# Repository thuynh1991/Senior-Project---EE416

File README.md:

# Senior-Project---EE416: Leak Detection System for the Robosub Autonomous Submarine
Ensuring the protection of electronics is an integral portion of any electromechanical system. Our project goal is to protect electronics within the hull of the WSU Robosub Club’s autonomous submarine, by implementing methods of leak detection. Providing information of an onboard leak allows for preventative action, and could potentiallysave thousands of dollars worth of material onboard. We have developed a two-part procedure to check, and monitor for potential leaks. This procedure consists of testing for leaks before the submarine is submerged, and is followed by an internal system that monitors water infiltration while underway. This project has met the needs and requirements set by our clients and stakeholders, while maintaining freedom of engineering design interpretation.<br /><br />
The DS_LC234X is FTDI - USB connector and we will use atmega1284P-AU chip for the project. <br />
EE415 code: Code to test the leak before submarine is submerged. <br />
EE416 code: Code for the internal(onboard) system. <br />  
Aruino Nano Shield: is our back up plan in case the internal system is fail.

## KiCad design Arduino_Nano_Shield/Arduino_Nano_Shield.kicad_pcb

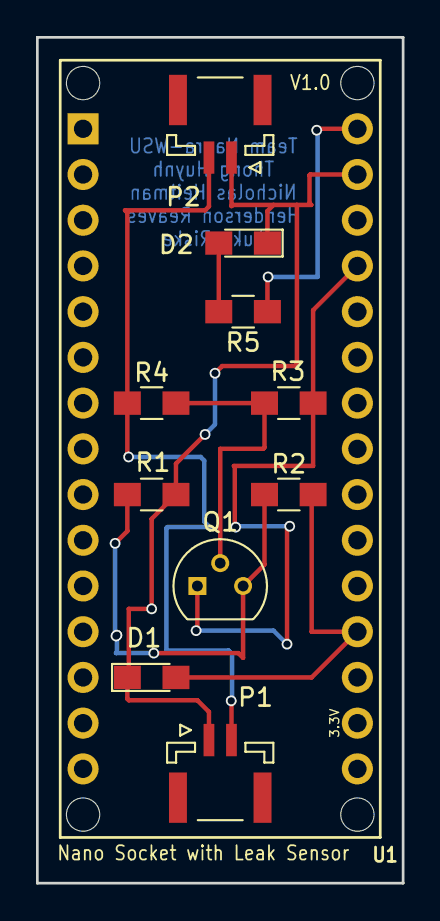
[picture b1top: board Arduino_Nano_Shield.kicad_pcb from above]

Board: 2 copper layers, 20.3 x 47.0 mm, 11 parts (0 on the bottom side), 8 nets.

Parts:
D1, D2: LED; LED_0805_HandSoldering
P1, P2: Probe_Port; JST_GH_SM02B-GHS-TB_02x1.25mm_Angled
Q1: 2N3906; TO-92_Molded_Narrow
R1, R4: 1K; R_0805_HandSoldering
R2, R5: 220; R_0805_HandSoldering
R3: 27K; R_0805_HandSoldering
U1: Arduino_Nano_Socket

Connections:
+5V: Q1.1, R3.1, U1.5V
/SIGNAL: D1.2, R2.2, U1.A0
GND: D1.1, D2.1, P1.1, P2.1, R1.2, U1.GND2
unnamed: D2.2, R5.2
unnamed: Q1.2, R3.2, R4.2
unnamed: Q1.3, R1.1, R2.1
PROBE: P1.2, P2.2, R4.1
VCC: R5.1, U1.VIN

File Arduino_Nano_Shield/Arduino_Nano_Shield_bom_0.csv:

Component,Description,Part,References,Value,Footprint,Quantity Per PCB,Datasheet,Digikey
1,LED generic,LED,D1 D2,LED,LED_0805_HandSoldering,4,,L62501CT-ND; 1516-1085-1-ND
2,,Probe_Port,P1 P2,Probe_Port,JST_GH_SM02B-GHS-TB_02x1.25mm_Angled,6,,455-1564-1-ND
3,"-40V Vce, -0.2A Ic, PNP, Small Signal Transistor, TO-92",2N3906,Q1,2N3906,TO-92_Molded_Narrow,2,https://www.fairchildsemi.com/datasheets/2N/2N3906.pdf,2N3906CS-ND
4,Resistor,R,R1 R4,1K,R_0805_HandSoldering,10,,P1.0KDACT-ND
5,Resistor,R,R2 R5,220,R_0805_HandSoldering,10,,408-1779-1-ND
6,Resistor,R,R3,27K,R_0805_HandSoldering,10,,P27KDACT-ND
7,,Arduino_Nano_Socket,U1,Arduino_Nano_Socket,Arduino_Nano_Socket,2,,S7013-ND 
,,,,,,,,
,,,,,,,,
,,,,,,,,
,,,,,,,,
,,,,,,,,
Component Groups:,7,,,,,,,
Component Count:,11,,,,,,,
Fitted Components:,11,,,,,,,
Number of PCBs:,1,,,,,,,
Total components:,11,,,,,,,
Schematic Version:,0,,,,,,,
Schematic Date:,3/25/2018,,,,,,,
BoM Date:,4/4/2018 23:13,,,,,,,
Schematic Source:,C:\Users\Thong_Huynh\Desktop\EE 416_new\Arduino_Nano_Shield\Arduino_Nano_Shield.sch,,,,,,,
KiCad Version:,Eeschema 4.0.7,,,,,,,

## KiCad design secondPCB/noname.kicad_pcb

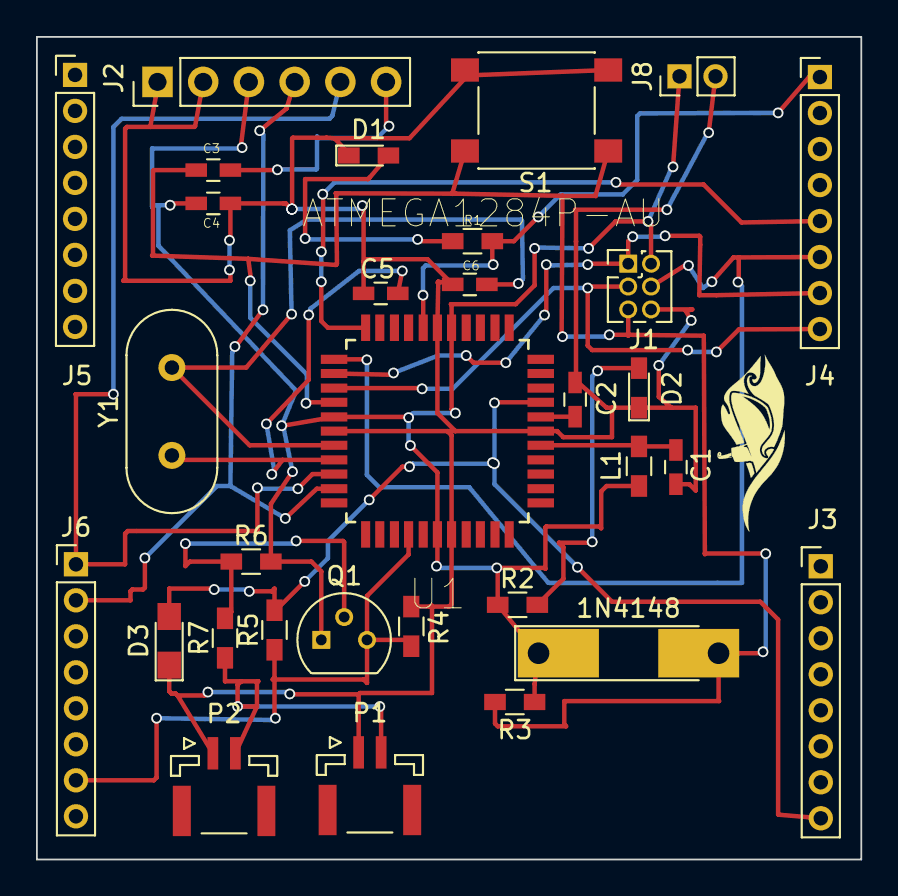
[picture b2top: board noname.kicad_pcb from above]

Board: 2 copper layers, 45.8 x 45.7 mm, 31 parts (0 on the bottom side), 21 nets.

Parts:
1N4148: D1; D_MELF-RM10_Universal_Handsoldering
C1: 100nF; C_0603_HandSoldering
C2, C4: 0.1uF; C_0603_HandSoldering
C3: 10uF; C_0603_HandSoldering
C5, C6: 22pF; C_0603_HandSoldering
D1, D2: LED_Small; LED_0603_HandSoldering
D3: LED; LED_0805_HandSoldering
J1: AVR_ISP; Pin_Header_Straight_2x03_Pitch1.27mm
J2: FTDI; Socket_Strip_Straight_1x06_Pitch2.54mm
J3: PortA; Pin_Header_Straight_1x08_Pitch2.00mm
J4: PortB; Pin_Header_Straight_1x08_Pitch2.00mm
J5: PortC; Pin_Header_Straight_1x08_Pitch2.00mm
J6: PortD; Pin_Header_Straight_1x08_Pitch2.00mm
J8: Power; Pin_Header_Straight_1x02_Pitch2.00mm
L1: 10uH; L_0603_HandSoldering
P1, P2: Probe_Port; JST_GH_SM02B-GHS-TB_02x1.25mm_Angled
Q1: 2N3906; TO-92_Molded_Narrow
R1: 330R; R_0603_HandSoldering
R2, R5: 220; R_0603_HandSoldering
R3: 10K; R_0603_HandSoldering
R4, R7: 1k; R_0603_HandSoldering
R6: 27k; R_0603_HandSoldering
S1: SW_Push; SW_SPST_PTS645
U1: ATMEGA1284P-AU; QFP80P1200X1200X120-44N
Y1: 16MHz; Crystal_HC49-U_Vertical

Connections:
/ANALOG_SIGNAL: D3.2, J3.8, R5.2, U1.30
/SIGNAL: J6.7, Q1.3, R4.1, R5.1, U1.15
AVCC: C1.1, L1.1, U1.27
GND: C1.2, C2.2, C3.2, C5.1, C6.1, D1.1, D2.1, D3.1, J1.6, J2.1, J2.2, J8.2, P1.1, P2.1, R4.2, S1.1, U1.6, U1.18, U1.28, U1.39
unnamed: C2.1, U1.29
unnamed: C4.1, J2.6
unnamed: D1.2, R1.1
unnamed: D2.2, R2.2
unnamed: Q1.2, R6.1, R7.2
PB0: J4.1, R1.2, U1.40
PB4: J4.5, U1.44
PB5: J1.4, J4.6, U1.1
PB6: J1.1, J4.7, U1.2
PB7: J1.3, J4.8, U1.3
PD0: J2.5, J6.1, U1.9
PD1: J2.4, J6.2, U1.10
PROBE: P1.2, P2.2, R7.1
RST: 1N4148.2, C4.2, J1.5, R3.1, S1.2, U1.4
VCC: 1N4148.1, C3.1, J1.2, J2.3, J8.1, L1.2, Q1.1, R2.1, R3.2, R6.2, U1.5, U1.17, U1.38
XTAL1: C5.2, U1.8, Y1.1
XTAL2: C6.2, U1.7, Y1.2

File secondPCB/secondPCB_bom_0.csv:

Component,Description,Part,References,Value,Footprint,Quantity Per PCB,Datasheet,Digikey
1,Diode,D,1N4148,D1,D_MELF-RM10_Universal_Handsoldering,1,,1N4148FS-ND
2,Unpolarized capacitor,C,C1 C2 C4,100nF,C_0603_HandSoldering,10,,445-5201-1-ND
3,Unpolarized capacitor,C,C3,10uF,C_0603_HandSoldering,10,,490-12317-1-ND
4,Unpolarized capacitor,C,C5 C6,22pF,C_0603_HandSoldering,10,,399-9030-1-ND
5,LED generic,LED,D3,LED,LED_0805_HandSoldering,1,,
6,"LED, small symbol",LED_Small,D1 D2,LED_Small,LED_0603_HandSoldering,10,,160-1448-1-ND 
7,,AVR_ISP,J1,AVR_ISP,Pin_Header_Straight_2x03_Pitch1.27mm,5,,S9015E-03-ND
8,"Generic connector, single row, 01x02",Conn_01x02,J8,Conn_01x02,Pin_Header_Straight_1x02_Pitch2.00mm,2,,S5800-02-ND
9,,FTDI-RESCUE-secondPCB,J2,FTDI,Socket_Strip_Straight_1x06_Pitch2.54mm,10,,S7039-ND
10,,PortA,J3,PortA,Pin_Header_Straight_1x08_Pitch2.00mm,4,,S5751-08-ND
11,,PortB,J4,PortB,Pin_Header_Straight_1x08_Pitch2.00mm,4,,S5751-08-ND
12,,PortC,J5,PortC,Pin_Header_Straight_1x08_Pitch2.00mm,1,,S5751-08-ND
13,,PortD,J6,PortD,Pin_Header_Straight_1x08_Pitch2.00mm,1,,S5751-08-ND
14,Inductor,L,L1,10uH,L_0603_HandSoldering,10,,587-1714-1-ND
15,,Probe_Port,P1 P2,Probe_Port,JST_GH_SM02B-GHS-TB_02x1.25mm_Angled,4,,455-1564-1-ND
16,"-40V Vce, -0.2A Ic, PNP, Small Signal Transistor, TO-92",2N3906,Q1,2N3906,TO-92_Molded_Narrow,2,https://www.fairchildsemi.com/datasheets/2N/2N3906.pdf,2N3906CS-ND
17,Resistor,R,R3,10K,R_0603_HandSoldering,10,,P20397CT-ND
18,Resistor,R,R4 R7,1k,R_0603_HandSoldering,10,,RHM1.0KDCT-ND
19,Resistor,R,R2 R5,220,R_0603_HandSoldering,10,,RHM220DCT-ND
20,Resistor,R,R6,27k,R_0603_HandSoldering,10,,RHM27.0KADCT-ND
21,Resistor,R,R1,330R,R_0603_HandSoldering,10,,RHM330DCT-ND
22,"Push button switch, generic, two pins",SW_Push,S1,SW_Push,SW_SPST_PTS645,10,,CKN9088CT-ND
23,,ATMEGA1284P-AU-RESCUE-secondPCB,U1,ATMEGA1284P-AU,QFP80P1200X1200X120-44N,2,,ATMEGA1284P-AU-ND
24,Two pin crystal,Crystal,Y1,16MHz,Crystal_HC49-4H_Vertical,10,,XC1748-ND
,,,,,,,,
,,,,,,,,
,,,,,,,,
,,,,,,,,
,,,,,,,,
Component Groups:,24,,,,,,,
Component Count:,31,,,,,,,
Fitted Components:,31,,,,,,,
Number of PCBs:,1,,,,,,,
Total components:,31,,,,,,,
Schematic Version:,0,,,,,,,
Schematic Date:,3/25/2018,,,,,,,
BoM Date:,4/7/2018 1:56,,,,,,,
Schematic Source:,C:\Users\Thong_Huynh\Desktop\secondPCB\secondPCB.sch,,,,,,,
KiCad Version:,Eeschema 4.0.7,,,,,,,

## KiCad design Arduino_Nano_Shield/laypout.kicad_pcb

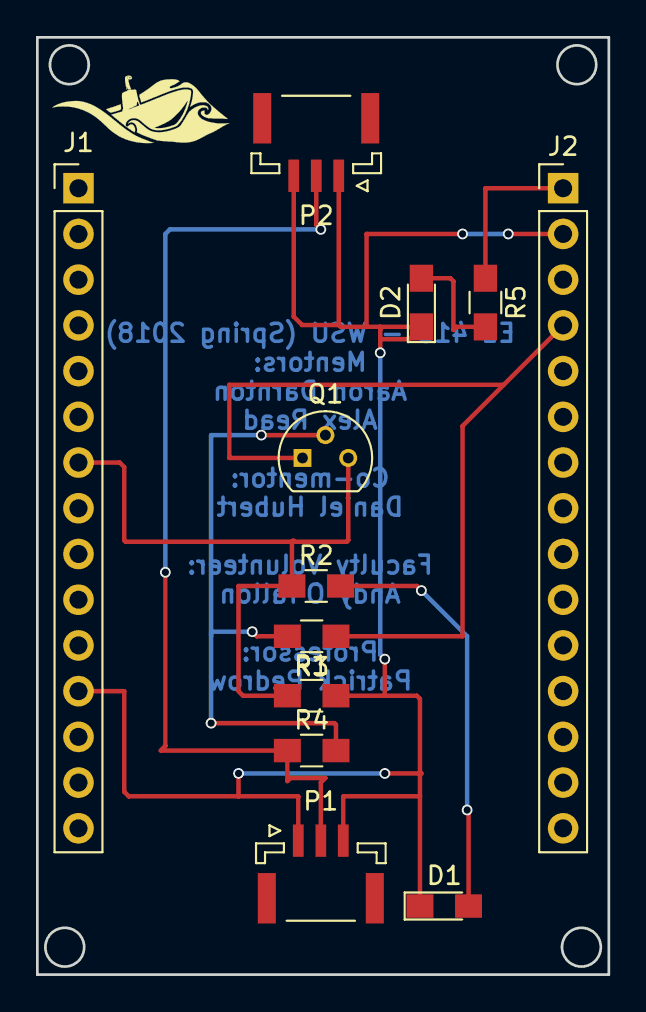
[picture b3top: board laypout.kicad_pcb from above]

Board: 2 copper layers, 31.8 x 52.1 mm, 12 parts (0 on the bottom side), 8 nets.

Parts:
D1, D2: LED; LED_0805_HandSoldering
J1: NANO_STRIP2; Pin_Header_Straight_1x15_Pitch2.54mm
J2: NANO_STRIP1; Pin_Header_Straight_1x15_Pitch2.54mm
P1, P2: Probe_Port; JST_GH_SM03B-GHS-TB_03x1.25mm_Angled
Q1: 2N3906; TO-92_Molded_Narrow
R1, R4: 1K; R_0805_HandSoldering
R2, R5: 220; R_0805_HandSoldering
R3: 27K; R_0805_HandSoldering

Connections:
+5V: J2.4, Q1.1, R3.1
/SIGNAL: J1.7, Q1.3, R1.1, R2.1
GND: D1.1, D2.1, J1.12, J2.2, P1.1, P1.3, P2.1, P2.3, R1.2
unnamed: D1.2, R2.2
unnamed: D2.2, R5.2
unnamed: Q1.2, R3.2, R4.2
PROBE: P1.2, P2.2, R4.1
VCC: J2.1, R5.1

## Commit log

2018-03-26 Create Backup Plan
2018-04-03 Create Arduino Nano Shield
2018-04-03 Add files via upload
    FTDI - USB connector
